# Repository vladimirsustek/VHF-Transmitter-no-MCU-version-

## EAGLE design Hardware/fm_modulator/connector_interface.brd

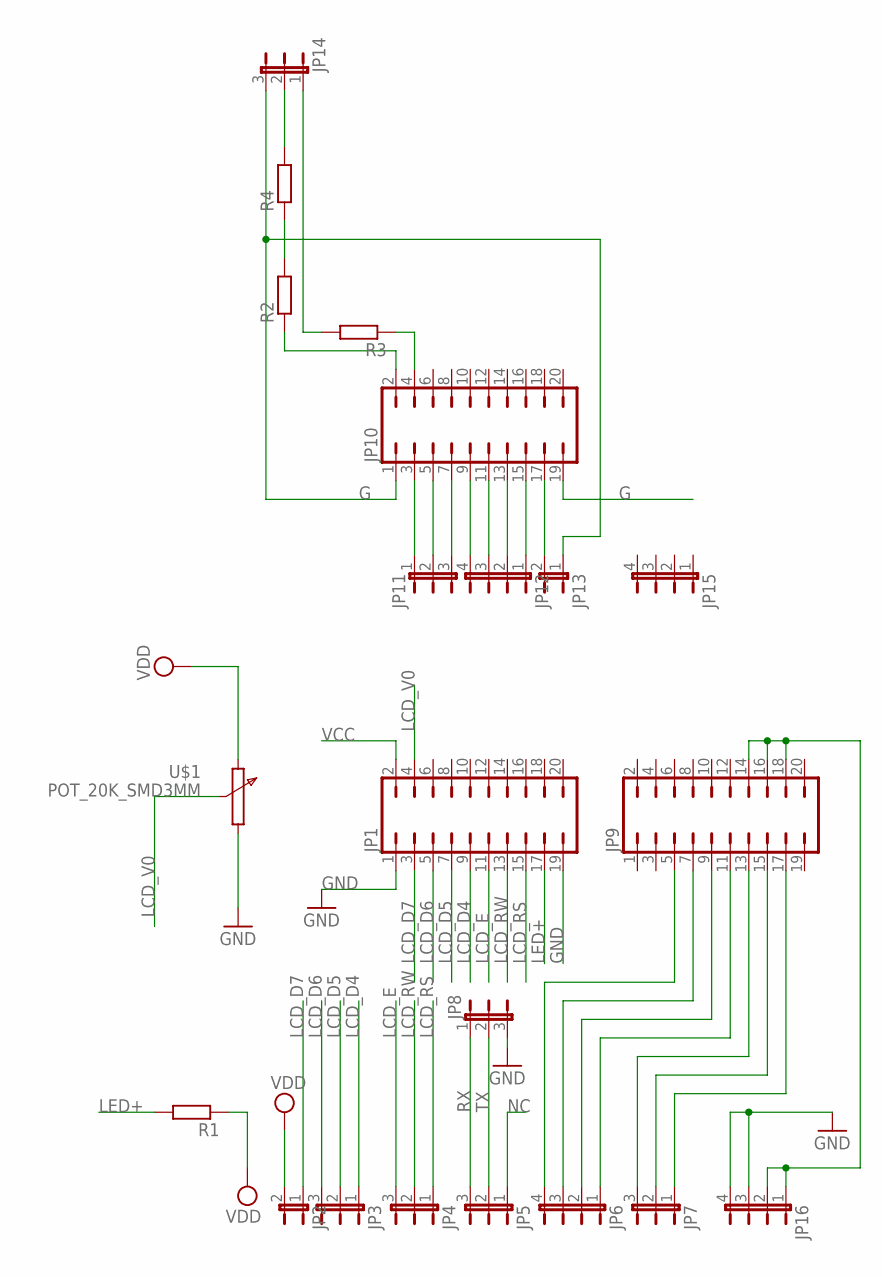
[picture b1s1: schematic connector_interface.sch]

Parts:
JP1, JP9, JP10: JP10Q
JP2, JP13: JP1E; JP1
JP3, JP4, JP5, JP7, JP8, JP11, JP14: JP2E; JP2
JP6, JP12, JP15, JP16: JP4E; JP4
R1, R2, R3, R4: R-EU_R1206; R1206
U$1: POT_20K_SMD3MM; POT_3MM_SMD

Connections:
G: JP10.1, JP10.19, JP13.1, JP14.3
GND: JP1.1, JP1.19, JP8.3, JP16.3, JP16.4, U$1.1
LCD_D4: JP1.9, JP3.1
LCD_D5: JP1.7, JP3.2
LCD_D6: JP1.5, JP3.3
LCD_D7: JP1.3, JP2.1
LCD_E: JP1.11, JP4.3
LCD_RS: JP1.15, JP4.1
LCD_RW: JP1.13, JP4.2
LCD_V0: JP1.4, U$1.2
LED+: JP1.17, R1.2
unnamed: JP7.1, JP9.17
unnamed: JP9.14, JP9.16, JP9.18, JP16.1, JP16.2
unnamed: JP10.2, R2.1
unnamed: JP14.1, R3.2
unnamed: JP10.9, JP12.4
unnamed: JP10.3, JP11.1
unnamed: JP10.5, JP11.2
unnamed: JP10.7, JP11.3
unnamed: JP10.17, JP13.2
unnamed: JP10.11, JP12.3
unnamed: JP10.13, JP12.2
unnamed: JP10.15, JP12.1
unnamed: JP6.4, JP9.5
unnamed: JP6.3, JP9.7
unnamed: JP6.2, JP9.9
unnamed: JP6.1, JP9.11
unnamed: JP7.3, JP9.13
unnamed: JP7.2, JP9.15
unnamed: JP14.2, R4.2
unnamed: JP10.4, R3.1
unnamed: R2.2, R4.1
NC: JP5.1
RX: JP5.3, JP8.1
TX: JP5.2, JP8.2
VCC: JP1.2
VDD: JP2.2, R1.1, U$1.3

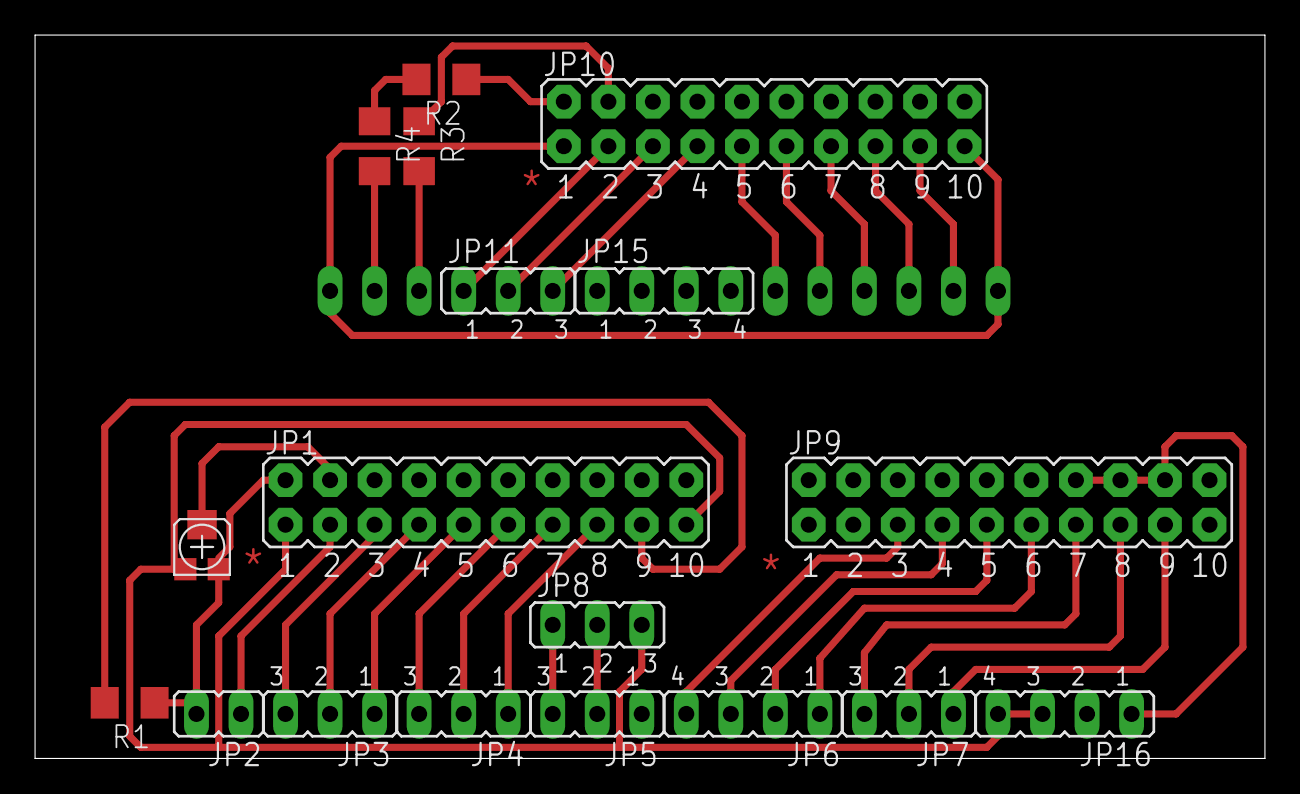
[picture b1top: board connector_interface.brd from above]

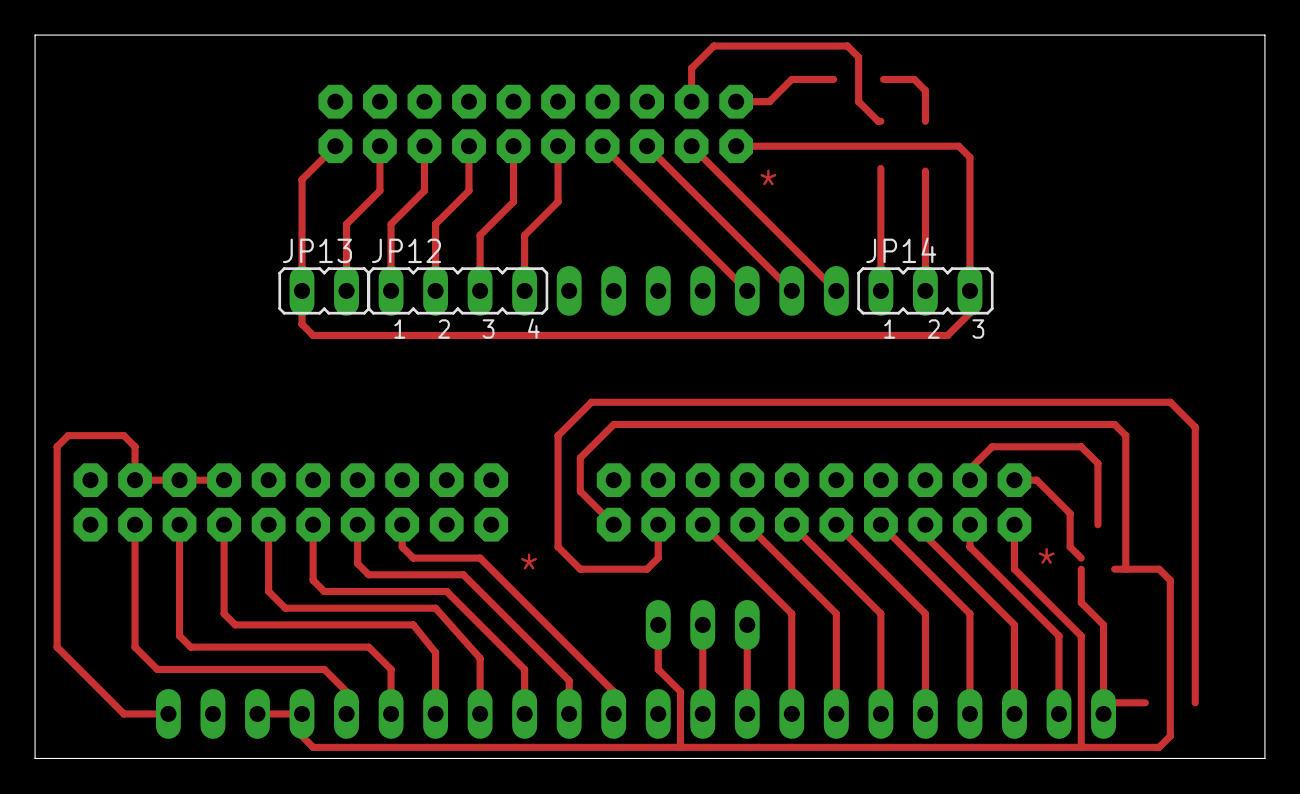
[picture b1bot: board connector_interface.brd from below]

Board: 2 copper layers, 70.2 x 41.3 mm, 21 parts (3 on the bottom side), 35 nets.

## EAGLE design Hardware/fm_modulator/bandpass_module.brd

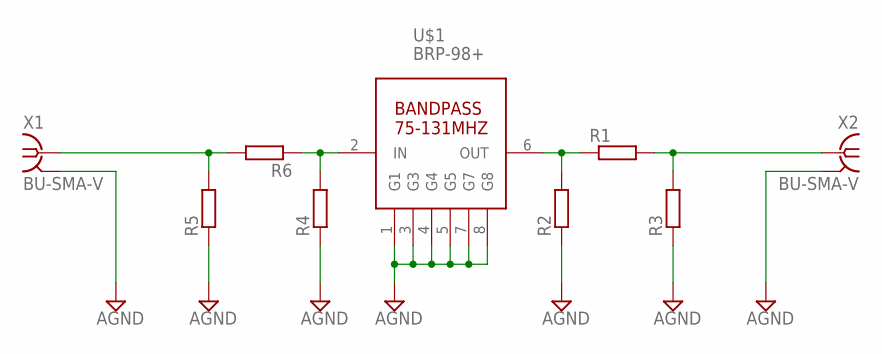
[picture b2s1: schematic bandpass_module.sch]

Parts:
R1, R2, R3, R4, R5, R6: R-EU_R0805; R0805
U$1: BRP-98+; RBP-98+
X1, X2: BU-SMA-V

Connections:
AGND: R2.1, R3.1, R4.1, R5.1, U$1.1 (G1), U$1.3 (G3), U$1.4 (G4), U$1.5 (G5), U$1.7 (G7), U$1.8 (G8), X1.2, X1.3 (2), X1.4 (2), X1.5 (2), X2.2, X2.3 (2), X2.4 (2), X2.5 (2)
unnamed: R4.2, R6.1, U$1.2 (IN)
unnamed: R5.2, R6.2, X1.1
unnamed: R1.1, R2.2, U$1.6 (OUT)
unnamed: R1.2, R3.2, X2.1

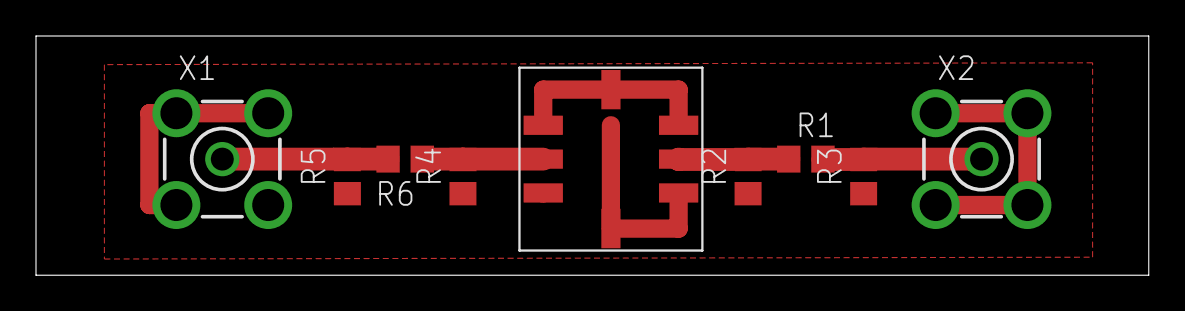
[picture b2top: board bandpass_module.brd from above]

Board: 2 copper layers, 61.8 x 13.3 mm, 9 parts (0 on the bottom side), 5 nets.

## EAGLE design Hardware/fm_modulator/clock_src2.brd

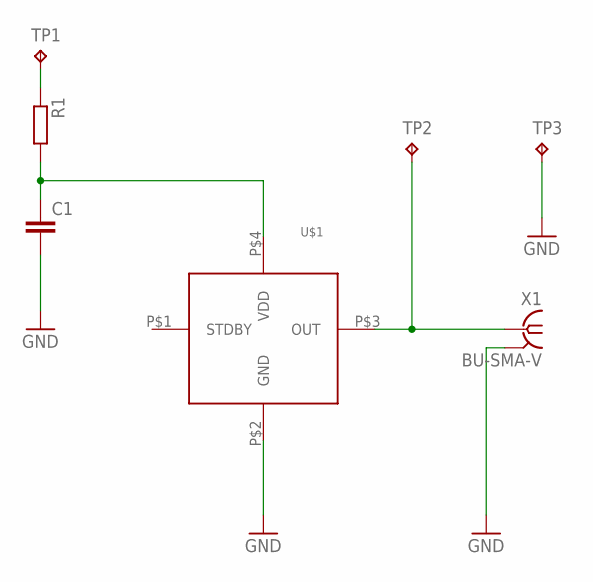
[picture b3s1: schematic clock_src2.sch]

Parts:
C1: C-EUC0603; C0603
R1: R-EU_R0603; R0603
TP1, TP2, TP3: TPTP20SQ; TP20SQ
U$1: ASFLMB-24525
X1: BU-SMA-V

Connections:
GND: C1.2, TP3.TP, U$1.P$2 (GND), X1.2, X1.3 (2), X1.4 (2), X1.5 (2)
unnamed: TP2.TP, U$1.P$3 (OUT), X1.1
unnamed: R1.1, TP1.TP
unnamed: C1.1, R1.2, U$1.P$4 (VDD)

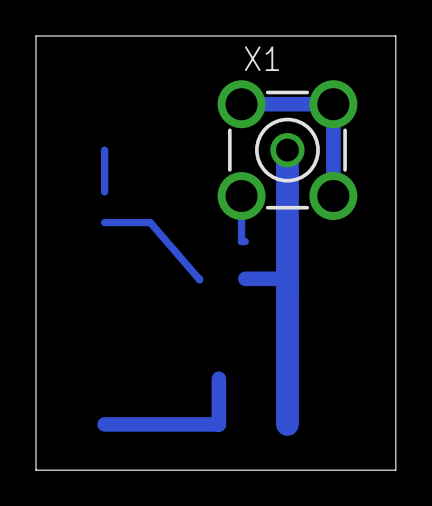
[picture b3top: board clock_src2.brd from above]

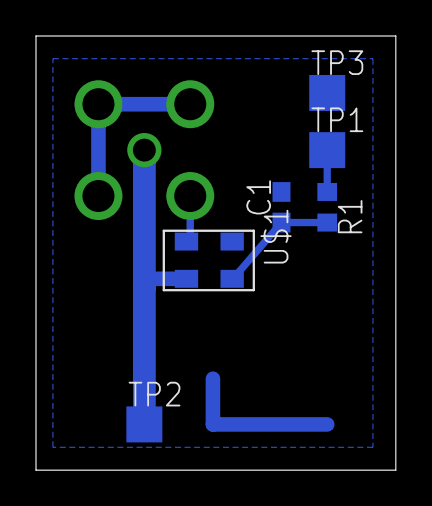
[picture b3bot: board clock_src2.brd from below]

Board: 2 copper layers, 20.0 x 24.1 mm, 7 parts (6 on the bottom side), 4 nets.

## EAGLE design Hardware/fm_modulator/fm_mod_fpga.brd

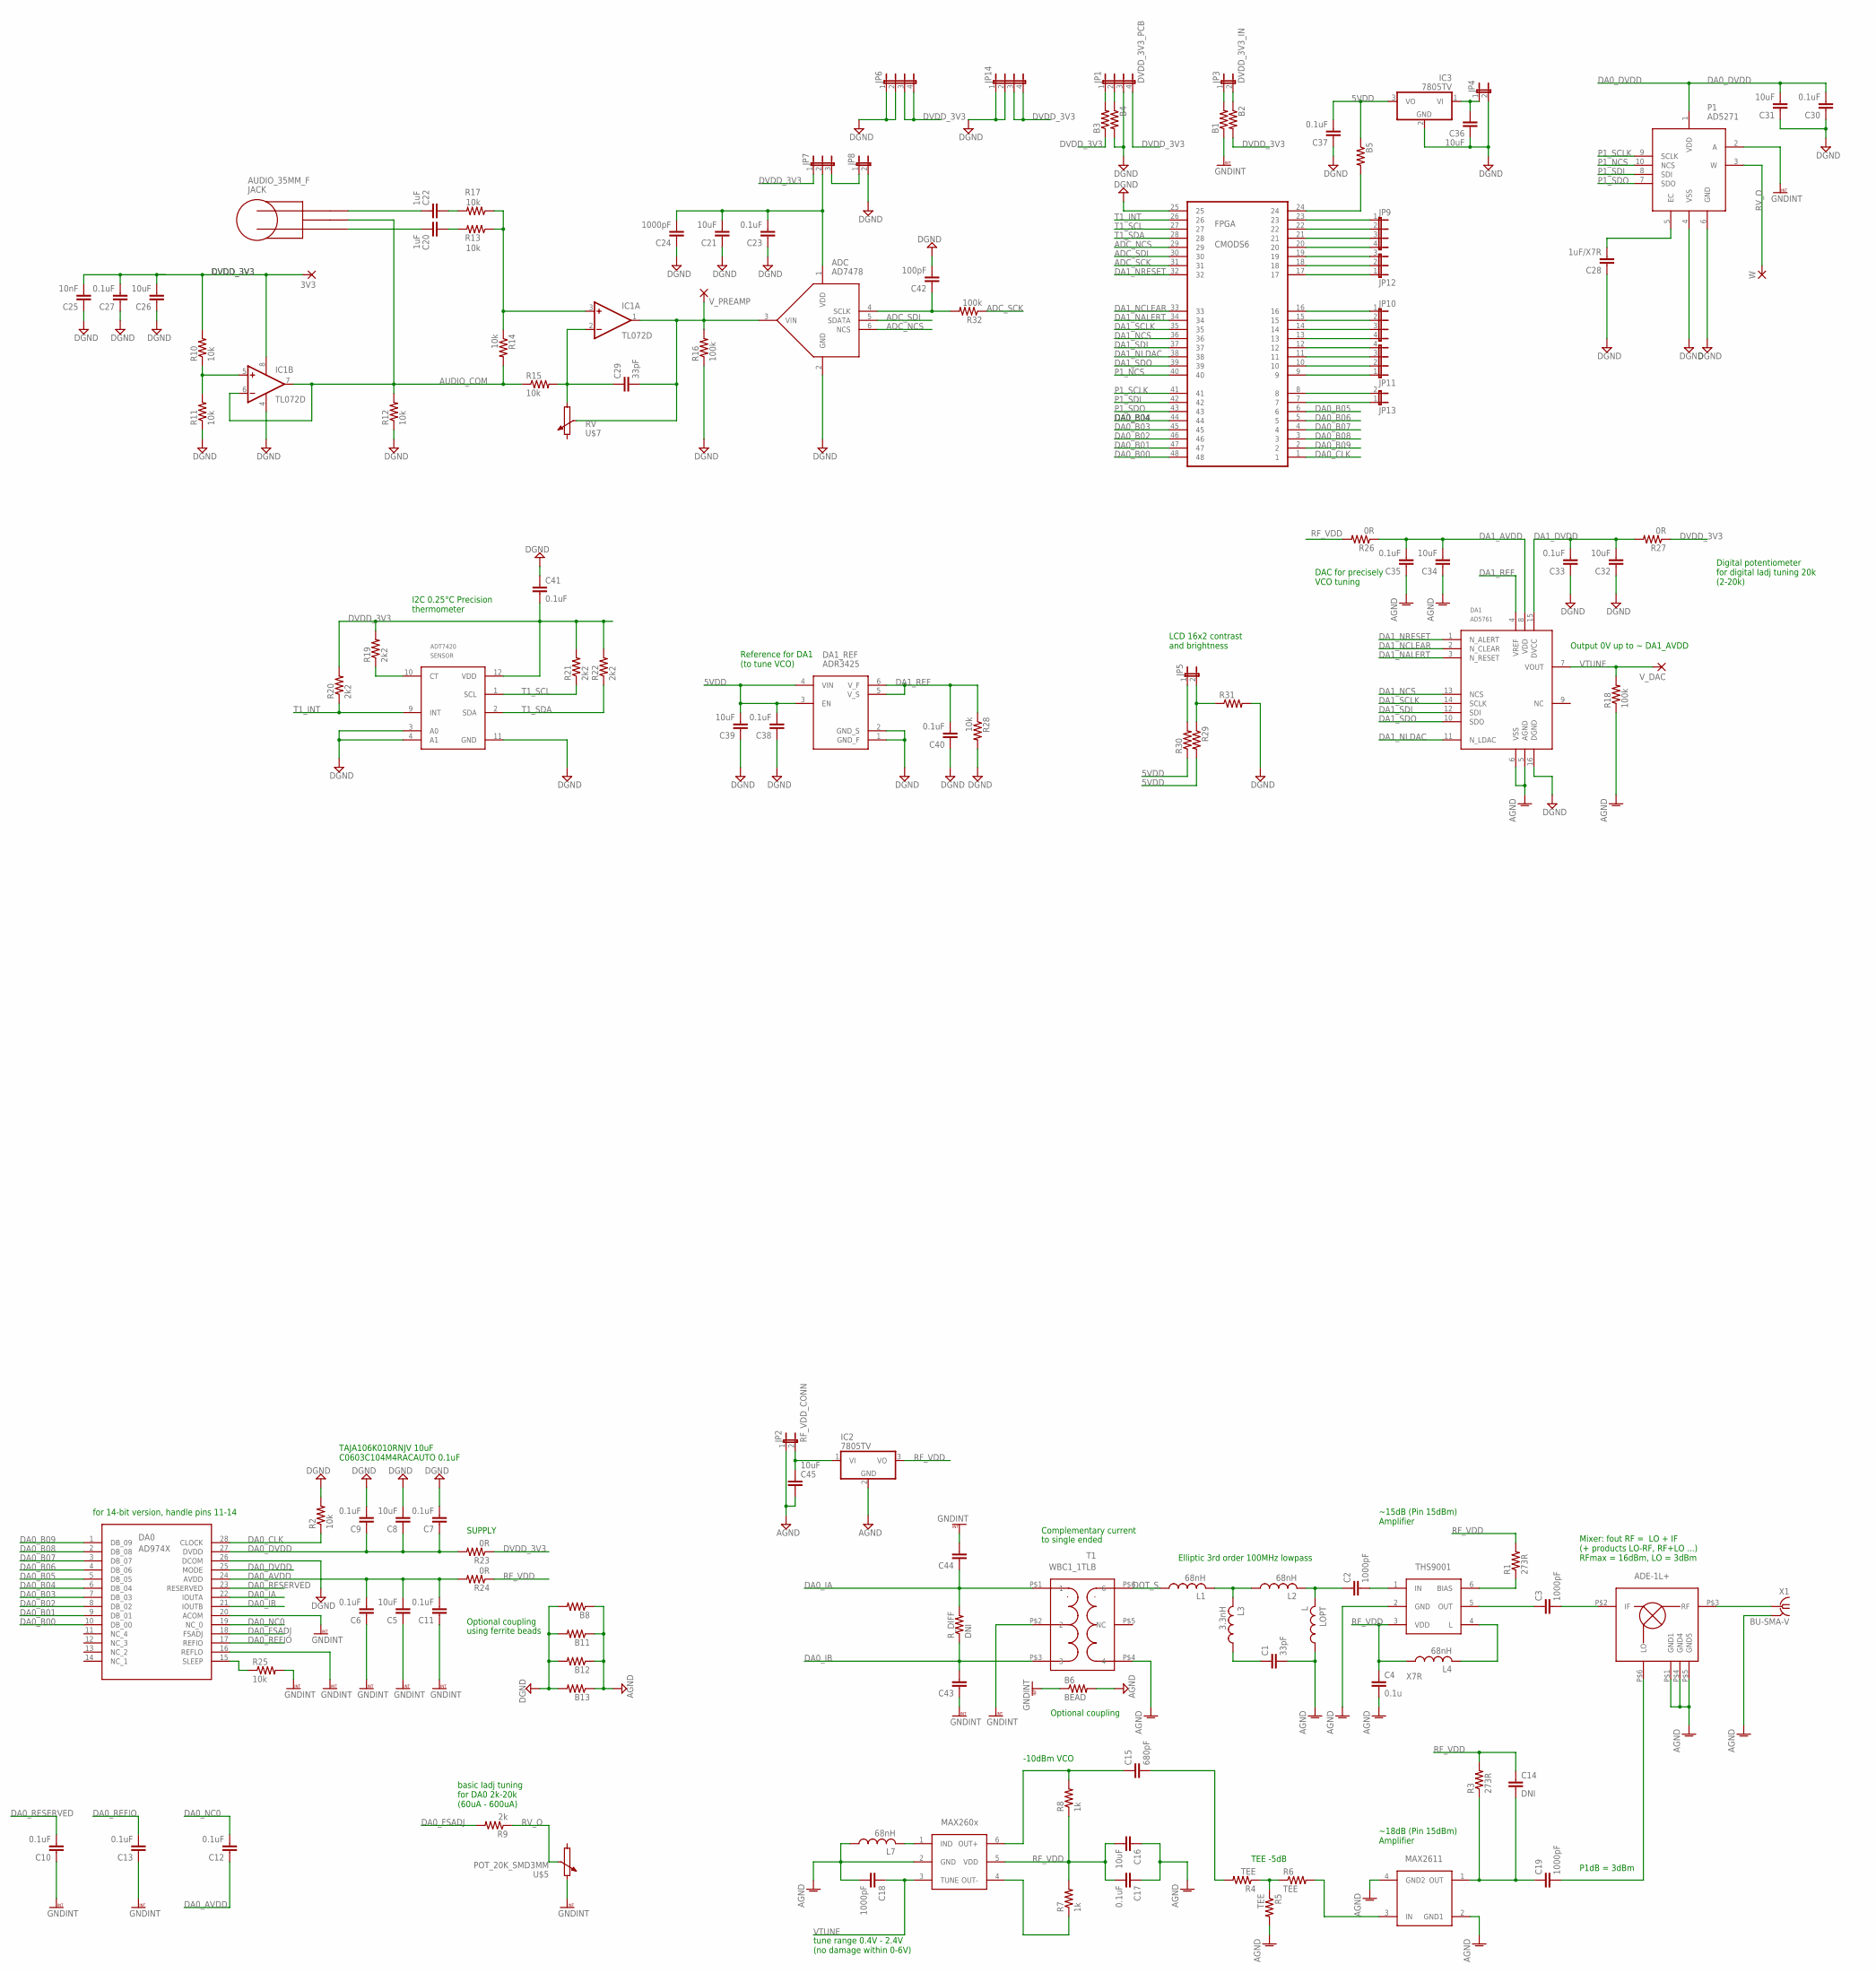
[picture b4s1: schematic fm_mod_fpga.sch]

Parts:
3V3: WIREPAD1,6/0,8; 1,6/0,8
ADC: AD7478; SOT23-6
B1, B2, B3, B4, B5, B8, B11, B12, B13: R-US_M0805; M0805
B6: BEAD; M0805
C1, C29: 33pF; C0603
C2, C3, C18, C19, C24: 1000pF; C0805
C4: 0.1u; C0805
C5, C8, C16, C21, C26, C31, C32, C34, C36, C39, C45: 10uF; C1206
C6, C7, C9, C10, C11, C12, C13, C17, C23, C27, C30, C33, C35, C37, C38, C40, C41: 0.1uF; C0603
C14: DNI; C0603
C15: 680pF; C0805
C20, C22: 1uF; C1206
C25: 10nF; C0805
C28: 1uF/X7R; C0805
C42: 100pF; C0603
C43, C44: C-EUC0402; C0402
DA0: AD974X; TSSOP28
DA1: AD5761; TSSOP-16
DA1_REF: ADR3425; SOT23-6
FPGA: CMODS6; CMODS6_DIP48
IC1: TL072D; SO08
IC2, IC3: 7805TV; TO220V
JACK: AUDIO_35MM_F
JP1: DVDD_3V3_PCB; JP4
JP2: RF_VDD_CONN; JP1
JP3: DVDD_3V3_IN; JP1
JP4, JP5, JP8, JP13: JP1E; JP1
JP6, JP9, JP10, JP11, JP14: JP4E; JP4
JP7, JP12: JP2E; JP2
L1, L2, L4, L7: 68nH; COILCRAFT_0805HP
L3: 3.3nH; COILCRAFT_0805HP
LOPT: L; COILCRAFT_0805HP
P1: AD5271; MSOP-10
R1, R3: 273R; R0805
R2, R10, R11, R12, R13, R14, R15, R17, R25, R28: 10k; R0805
R4, R5, R6: TEE; R0805
R7, R8: 1k; R0805
R9: 2k; R0805
R16, R18, R32: 100k; R0805
R19, R20, R21, R22: 2k2; R0805
R23, R24, R26, R27: 0R; R0805
R29, R30, R31: R-US_R0805; R0805
R_DIFF: DNI; R0603
SENSOR: ADT7420; LFCSP-16
T1: WBC1_1TLB; WBC1_1
U$2: THS9001; SOT23-6
U$3: MAX2611; SOT143-4
U$4: MAX260X; SOT23-6
U$5: POT_20K_SMD3MM; POT_3MM_SMD
U$6: ADE-1L+
U$7: RV
V_DAC: WIREPAD1,6/0,8; 1,6/0,8
V_PREAMP: WIREPAD1,6/0,8; 1,6/0,8
W: WIREPAD1,6/0,8; 1,6/0,8
X1: BU-SMA-V

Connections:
5VDD: B5.1, C37.2, C38.2, C39.2, DA1_REF.3 (EN), DA1_REF.4 (VIN), IC3.3 (VO), R29.2, R30.1
100K: ADC.3 (VIN), C29.2, IC1.1 (OUT), R16.2, U$7.2, V_PREAMP.1
ADC_NCS: ADC.6 (NCS), FPGA.29
ADC_SCK: FPGA.31, R32.1
ADC_SDI: ADC.5 (SDATA), FPGA.30
AGND: B6.2, B8.1, B11.1, B12.1, B13.1, C1.2, C4.2, C16.1, C17.1, C18.2, C34.1, C35.1, C45.2, DA1.5 (AGND), DA1.6 (VSS), IC2.2 (GND), JP2.1, L7.1, LOPT.1, R5.2, R18.1, T1.P$4 (4), U$2.2 (GND), U$3.2 (GND1), U$3.4 (GND2), U$4.2 (GND), U$6.P$1 (GND1), U$6.P$4 (GND4), U$6.P$5 (GND5), X1.2, X1.3 (2), X1.4 (2), X1.5 (2)
AUDIO_COM: IC1.6 (-IN), IC1.7 (OUT), JACK.1, R12.2, R14.2, R15.1
DA0_AVDD: C5.2, C6.2, C11.2, C12.1, DA0.24 (AVDD), R24.2
DA0_B00: DA0.10 (DB_00), FPGA.48
DA0_B01: DA0.9 (DB_01), FPGA.47
DA0_B02: DA0.8 (DB_02), FPGA.46
DA0_B03: DA0.7 (DB_03), FPGA.45
DA0_B04: DA0.6 (DB_04), FPGA.44
DA0_B05: DA0.5 (DB_05), FPGA.6
DA0_B06: DA0.4 (DB_06), FPGA.5
DA0_B07: DA0.3 (DB_07), FPGA.4
DA0_B08: DA0.2 (DB_08), FPGA.3
DA0_B09: DA0.1 (DB_09), FPGA.2
DA0_CLK: DA0.28 (CLOCK), FPGA.1, R2.1
DA0_DVDD: C7.1, C8.1, C9.1, C30.2, C31.2, DA0.25 (MODE), DA0.27 (DVDD), P1.1 (VDD), R23.2
DA0_FSADJ: DA0.18 (FSADJ), R9.2
DA0_IA: C44.1, DA0.22 (IOUTA), R_DIFF.2, T1.P$1 (1)
DA0_IB: C43.2, DA0.21 (IOUTB), R_DIFF.1, T1.P$3 (3)
DA0_NC0: C12.2, DA0.19 (NC_0)
DA0_REFIO: C13.2, DA0.17 (REFIO)
DA0_RESERVED: C10.2, DA0.23 (RESERVED)
DA0_SLEEP: DA0.15 (SLEEP), R25.1
DA1_AVDD: C34.2, C35.2, DA1.8 (VDD), R26.1
DA1_DVDD: C32.2, C33.2, DA1.15 (DVCC), R27.2
DA1_NALERT: DA1.3 (N_RESET), FPGA.34
DA1_NCLEAR: DA1.2 (N_CLEAR), FPGA.33
DA1_NCS: DA1.13 (NCS), FPGA.36
DA1_NLDAC: DA1.11 (N_LDAC), FPGA.38
DA1_NRESET: DA1.1 (N_ALERT), FPGA.32
DA1_REF: C40.2, DA1.4 (VREF), DA1_REF.5 (V_S), DA1_REF.6 (V_F), R28.1
DA1_SCLK: DA1.14 (SCLK), FPGA.35
DA1_SDI: DA1.12 (SDI), FPGA.37
DA1_SDO: DA1.10 (SDO), FPGA.39
DGND: ADC.2 (GND), B4.2, B8.2, B11.2, B12.2, B13.2, C7.2, C8.2, C9.2, C21.1, C23.1, C24.1, C25.1, C26.1, C27.1, C28.1, C30.1, C31.1, C32.1, C33.1, C36.1, C37.1, C38.1, C39.1, C40.1, C41.1, C42.2, DA0.26 (DCOM), DA1.16 (DGND), DA1_REF.1 (GND_F), DA1_REF.2 (GND_S), FPGA.25, IC1.4 (V-), IC3.2 (GND), JP1.3, JP4.2, JP6.1, JP6.2, JP8.2, JP14.1, JP14.2, P1.4 (VSS), P1.6 (GND), R2.2, R11.1, R12.1, R16.1, R28.2, R31.2, SENSOR.3 (A0), SENSOR.4 (A1), SENSOR.11 (GND)
DOT_S: L1.1, T1.P$6 (6)
DVDD_3V3: 3V3.1, B2.2, B3.1, C25.2, C26.2, C27.2, C41.2, IC1.8 (V+), JP1.4, JP6.3, JP6.4, JP7.1, JP14.3, JP14.4, R10.2, R19.2, R20.2, R21.2, R22.2, R23.1, R27.1, SENSOR.12 (VDD)
GNDINT: B1.1, B6.1, C5.1, C6.1, C10.1, C11.1, C13.1, C43.1, C44.2, DA0.16 (REFLO), DA0.20 (ACOM), P1.2 (A), R25.2, T1.P$2 (2), U$5.3
unnamed: C15.1, R8.2, U$4.6 (OUT+)
unnamed: U$6.P$3 (RF), X1.1
unnamed: C1.1, L3.1
unnamed: L1.2, L2.1, L3.2
unnamed: C15.2, R4.2
unnamed: C2.1, L2.2, LOPT.2
unnamed: C2.2, U$2.1 (IN)
unnamed: R1.1, U$2.6 (BIAS)
unnamed: C3.1, U$2.5 (OUT)
unnamed: L4.2, U$2.4 (L)
unnamed: C22.1, JACK.3
unnamed: C14.2, C19.1, R3.1, U$3.1 (OUT)
unnamed: R7.1, U$4.4 (OUT-)
unnamed: R6.2, U$3.3 (IN)
unnamed: C19.2, U$6.P$6 (LO)
unnamed: R4.1, R5.1, R6.1
unnamed: L7.2, U$4.1 (IND)
unnamed: C3.2, U$6.P$2 (IF)
unnamed: B1.2, JP3.1
unnamed: ADC.1 (VDD), C21.2, C23.2, C24.2, JP7.2
unnamed: ADC.4 (SCLK), C42.1, R32.2
unnamed: JP7.3, JP8.1
unnamed: FPGA.8, JP13.2
unnamed: B2.1, JP3.2
unnamed: B3.2, JP1.1
unnamed: B4.1, JP1.2
unnamed: IC1.3 (+IN), R13.1, R14.1, R17.1
unnamed: IC1.5 (+IN), R10.1, R11.2
unnamed: C20.2, JACK.2
unnamed: C29.1, IC1.2 (-IN), R15.2, U$7.1
unnamed: C22.2, R17.2
unnamed: C20.1, R13.2
unnamed: FPGA.7, JP13.1
unnamed: FPGA.16, JP10.1
unnamed: C45.1, IC2.1 (VI), JP2.2
unnamed: FPGA.15, JP10.2
unnamed: FPGA.14, JP10.3
unnamed: C28.2, P1.5 (EC)
unnamed: C36.2, IC3.1 (VI), JP4.1
unnamed: JP5.1, R30.2
unnamed: JP5.2, R29.1, R31.1
unnamed: FPGA.13, JP10.4
unnamed: R19.1, SENSOR.10 (CT)
unnamed: FPGA.9, JP11.1
unnamed: FPGA.10, JP11.2
unnamed: FPGA.23, JP9.1
unnamed: FPGA.22, JP9.2
unnamed: FPGA.21, JP9.3
unnamed: FPGA.20, JP9.4
unnamed: FPGA.17, JP12.1
unnamed: FPGA.18, JP12.2
unnamed: FPGA.19, JP12.3
unnamed: FPGA.11, JP11.3
unnamed: FPGA.12, JP11.4
unnamed: B5.2, FPGA.24
P1_NCS: FPGA.40, P1.10 (NCS)
P1_SCLK: FPGA.41, P1.9 (SCLK)
P1_SDI: FPGA.42, P1.8 (SDI)
P1_SDO: FPGA.43, P1.7 (SDO)
RF_VDD: C4.1, C14.1, C16.2, C17.2, IC2.3 (VO), L4.1, R1.2, R3.2, R7.2, R8.1, R24.1, R26.2, U$2.3 (VDD), U$4.5 (VDD)
RV_O: P1.3 (W), R9.1, U$5.2, W.1
T1_INT: FPGA.26, R20.1, SENSOR.9 (INT)
T1_SCL: FPGA.27, R21.1, SENSOR.1 (SCL)
T1_SDA: FPGA.28, R22.1, SENSOR.2 (SDA)
VTUNE: C18.1, DA1.7 (VOUT), R18.2, U$4.3 (TUNE), V_DAC.1

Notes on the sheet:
X7R
TAJA106K010RNJV 10uF C0603C104M4RACAUTO 0.1uF
for 14-bit version, handle pins 11-14
SUPPLY
I2C 0.25°C Precision thermometer
Reference for DA1 (to tune VCO)
DAC for precisely VCO tuning
basic Iadj tuning for DA0 2k-20k (60uA - 600uA)
Digital potentiometer for digital Iadj tuning 20k (2-20k)
Output 0V up to ~ DA1_AVDD
tune range 0.4V - 2.4V (no damage within 0-6V)
Elliptic 3rd order 100MHz lowpass
Mixer: fout RF = LO + IF (+ products LO-RF, RF+LO ...) RFmax = 16dBm, LO = 3dBm
~15dB (Pin 15dBm) Amplifier
~18dB (Pin 15dBm) Amplifier
-10dBm VCO
P1dB = 3dBm
TEE -5dB
LCD 16x2 contrast and brightness
Optional coupling
using ferrite beads
Complementary current
to single ended

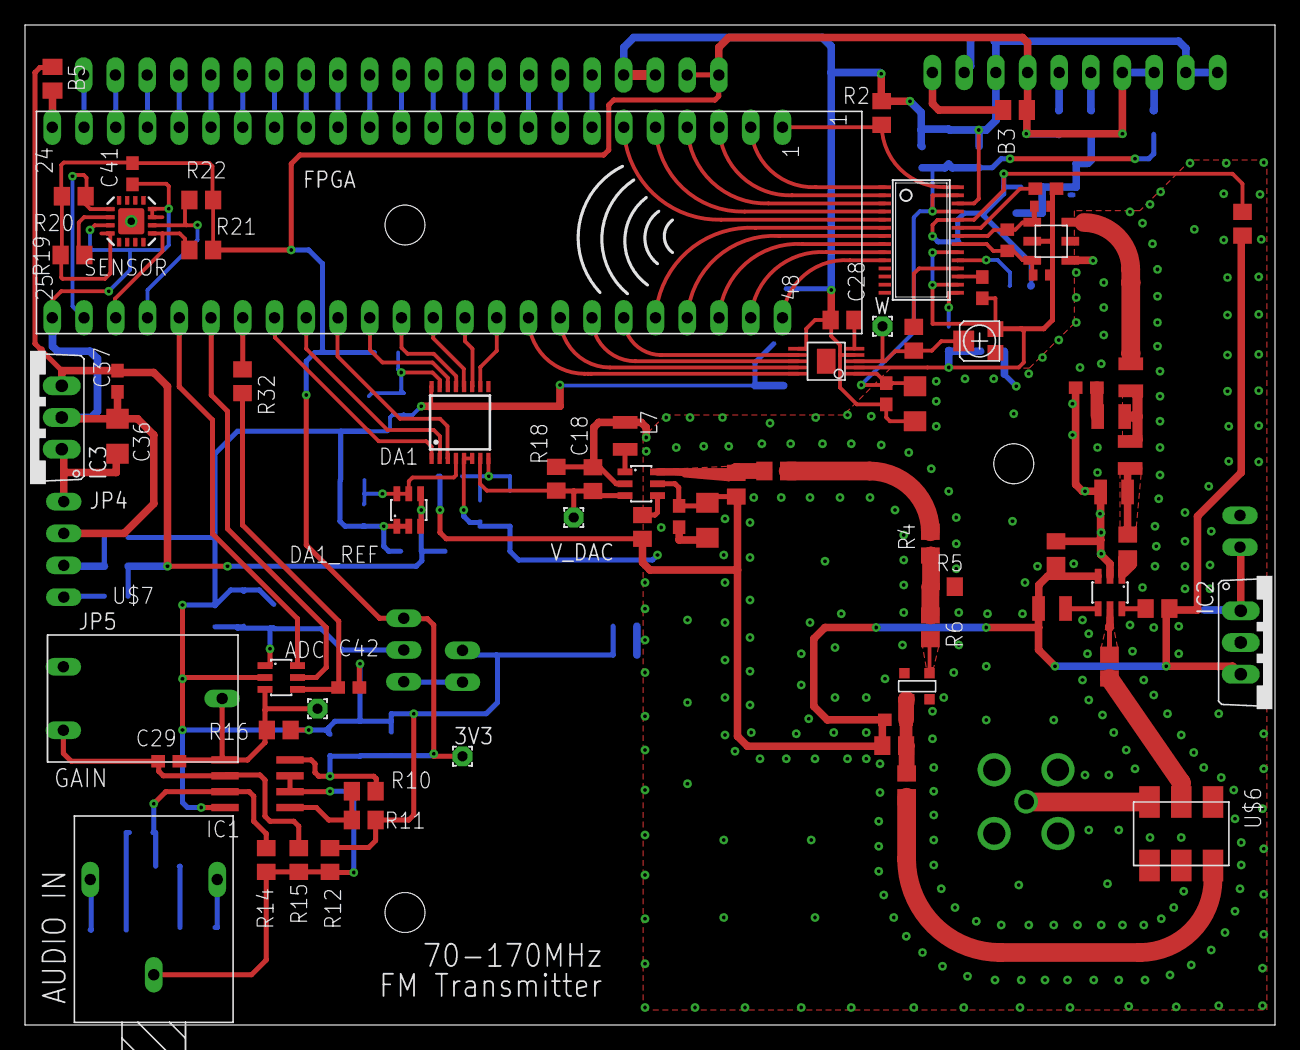
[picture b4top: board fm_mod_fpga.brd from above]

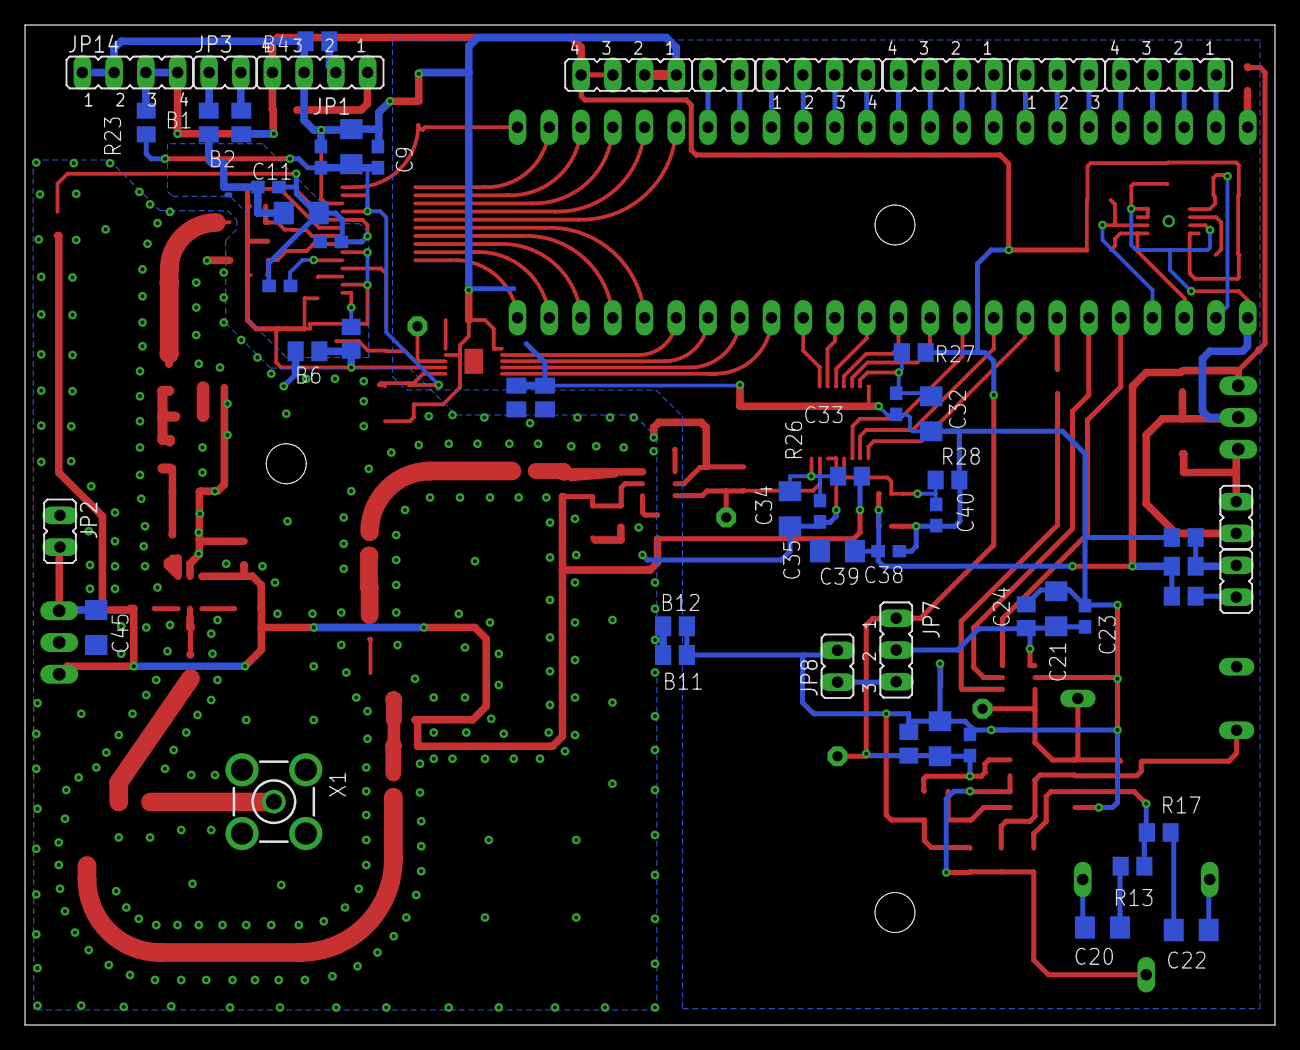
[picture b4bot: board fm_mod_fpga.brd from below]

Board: 2 copper layers, 100.0 x 80.0 mm, 131 parts (56 on the bottom side), 107 nets.

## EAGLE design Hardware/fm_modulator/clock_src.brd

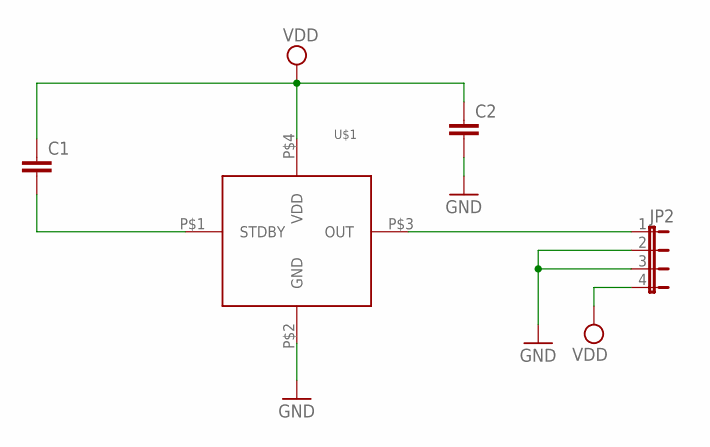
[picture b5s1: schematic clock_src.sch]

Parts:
C1, C2: C-EUC0603; C0603
JP2: JP4E; JP4
U$1: ASFLMB-24525

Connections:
GND: C2.2, JP2.2, JP2.3, U$1.P$2 (GND)
unnamed: JP2.1, U$1.P$3 (OUT)
unnamed: C1.2, U$1.P$1 (STDBY)
VDD: C1.1, C2.1, JP2.4, U$1.P$4 (VDD)

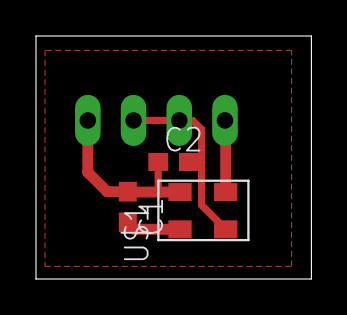
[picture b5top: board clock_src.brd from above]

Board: 2 copper layers, 15.3 x 13.5 mm, 4 parts (1 on the bottom side), 4 nets.

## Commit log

2021-05-02 Creating the repository (no code yet)
2021-05-02 Initial commit of VHF-Transmitter capable of: Mono transmission for frequency 92.2MHz when: - twice pressed both buttons (the LD0 on only) - three times clicked BTN0 (twice DAC0 freq decrease) When p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
    Commit contains .bit and .mcs files for Impact tool PFGA flashing
2021-05-31 Official V_Sustek_VHF-Transmitter_HW_V1.03.pdf enclosed
2021-06-08 Minor changes: added: da1_interface reset
    testbenches/
    testbenches/tb_da1_interface to confirm da1_interface functionality
    bitstream on physical device works as previous
2021-06-08 FW slightly change with capability of:
    - broadcast on frequency 92.2MHz right after startup
    - when GPIO09(L13) and GPIO10(K13) jumper:
    when jumper is placed, the ADC1 is selected:
    (tested with external board with ADC)
    NCS GPIO23(C13)
    SDO GPIO22(D13)
2021-06-10 Mono sound ADC0 + ADC1, clk_enabler optimization
2021-06-10 New features added: - SYS_RST GPIO7(L14)
2021-06-10 STABLE COMMIT - L+F MONO
    DONE:
    - fixed DAC1 failure by assigning input ports: PORTE, PORTD
    (leaving ports unassigned probably caused DAC1 shortcut)
    - simplified keyboard_interface by reducing controlled values:
    DAC0=>DDS PhInc: 50Khz step (on reset set to 21.1MHz)
    DAC1 voltage: 25mV step (on reset set to 625mV)
2021-11-24 DONE: - Added Hardware folder with PCB eagle project, schematics - fixed DAC1 failure by assigning input ports: PORTE, PORTD (leaving ports unassigned probably caused DAC1 shortcut) - simplified keyb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
2021-11-25 Attempt to add 19kHz pilot, weird functionality (touching contacts)
